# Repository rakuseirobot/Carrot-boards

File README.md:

# Carrot-boards
全自動走行台車の回路図です。
[Carrotの動画はこちら](https://www.youtube.com/watch?v=5gtot_12dCg&ab_channel=DDProjectII)

# Features

* STM32F7 Discovery用のボード
* KeyHolder FT234を使ったUSBシリアル変換器
* UI 操作板の基板データ　F4書き込みや、電源、リセットスイッチなどを載せる
* mainboard main基板　raspberryPiやSTM32F4が載ります

# Requirement

* Autodesk Eagleを用いて作成しました。

F4のプログラムは[こちら](https://github.com/rakuseirobot/Carrot-F4-motor)
RaspberryPiのプログラムは[こちら](https://github.com/rakuseirobot/Carrot-ROS-src)

# Note

mainboardに搭載されているSTM32F446に配線されているイーサネットICはLANコネクタを向きを逆に配置してしまったこととおそらく配線を間違ってしまったこともあり、実装すると3.3Vラインがショートしてしまうため注意してください。

# Author

* Shun Kayaki
* Kyushu institute of Technology
* shun@guetan.dev

# License

Copyright (c) 2019 Shun Kayaki
Released under the MIT license

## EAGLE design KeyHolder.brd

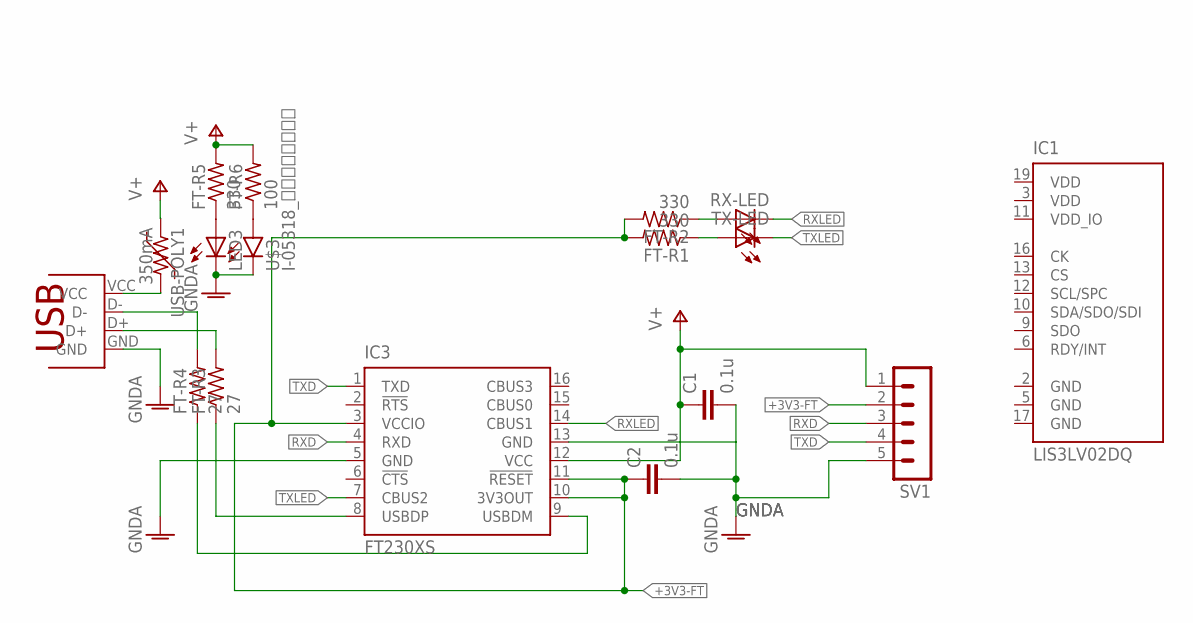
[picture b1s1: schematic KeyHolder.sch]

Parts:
C1, C2: 0.1u; C1608
FT-R1, FT-R2, FT-R5: 330; R0805
FT-R3, FT-R4: 27; R0805
FT-R6: 100; R0805
IC1: LIS3LV02DQ; QFPN-28
IC3: FT230XS; SSOP16
LED3: LEDCHIP-LED0805; CHIP-LED0805
RX-LED: LEDCHIP-LED0805; CHIP-LED0805
SV1: MA05-1
TX-LED: LEDCHIP-LED0805; CHIP-LED0805
U$2: USB-PAD; USB
U$3: I-05318_ＮＳＳＷ１５７Ｔ; NSSW157T
USB-POLY1: 350mA; F0805MP

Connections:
+3V3-FT: C2.1, FT-R1.2, FT-R2.2, IC3.3 (VCCIO), IC3.10 (3V3OUT), IC3.11 (!RESET), SV1.2
GND: IC1.2 (GND), IC1.5 (GND), IC1.17 (GND)
GNDA: C1.2, C2.2, IC3.5 (GND), IC3.13 (GND), LED3.C, SV1.5, U$2.GND, U$3.CATHODE (C)
unnamed: FT-R2.1, RX-LED.A
unnamed: FT-R1.1, TX-LED.A
unnamed: FT-R3.2, U$2.D+
unnamed: FT-R3.1, IC3.8 (USBDP)
unnamed: FT-R4.1, IC3.9 (USBDM)
unnamed: FT-R4.2, U$2.D-
unnamed: U$2.VCC, USB-POLY1.2
unnamed: FT-R5.1, LED3.A
unnamed: FT-R6.1, U$3.ANODE (A)
RXD: IC3.4 (RXD), SV1.3
RXLED: IC3.14 (CBUS1), RX-LED.C
TXD: IC3.1 (TXD), SV1.4
TXLED: IC3.7 (CBUS2), TX-LED.C
V+: C1.1, FT-R5.2, FT-R6.2, IC3.12 (VCC), SV1.1, USB-POLY1.1
VDD: IC1.3 (VDD), IC1.19 (VDD)
VDD_IO: IC1.11 (VDD_IO)

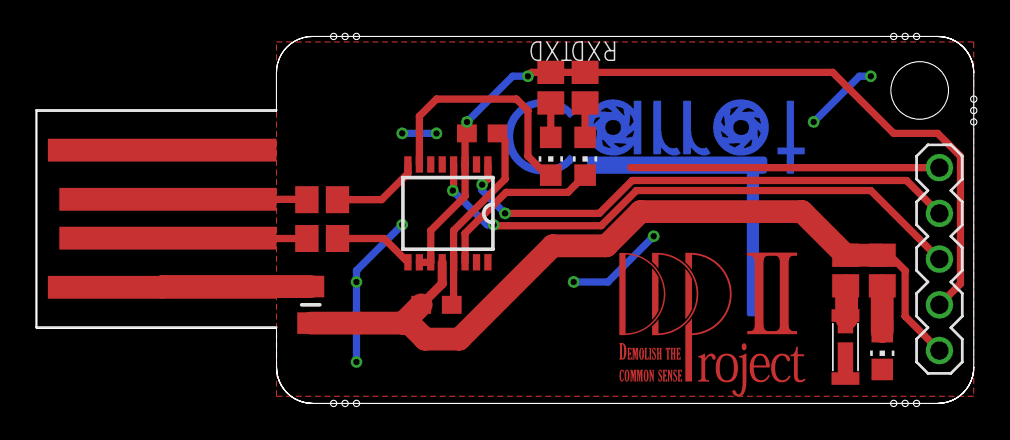
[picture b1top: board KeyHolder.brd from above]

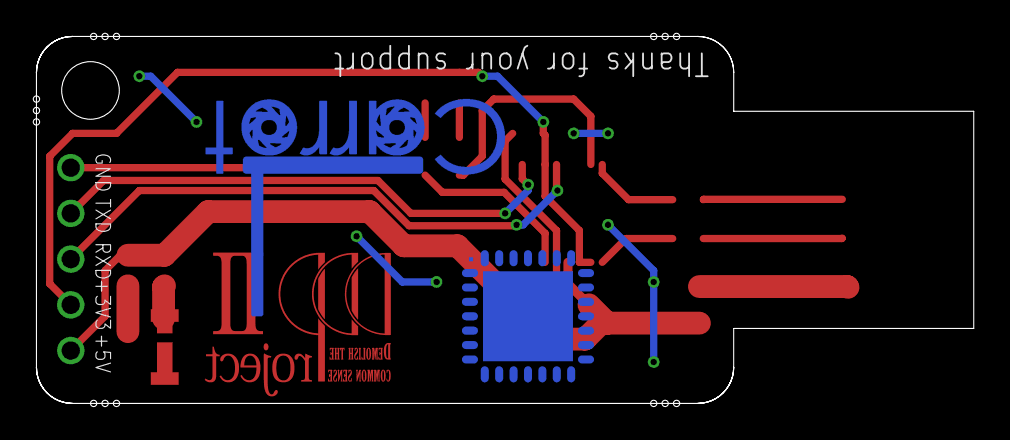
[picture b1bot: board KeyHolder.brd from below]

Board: 2 copper layers, 52.1 x 20.4 mm, 19 parts (2 on the bottom side), 18 nets.

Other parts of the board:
U$5: CARROT
U$6: DDPROJECT2-TOP

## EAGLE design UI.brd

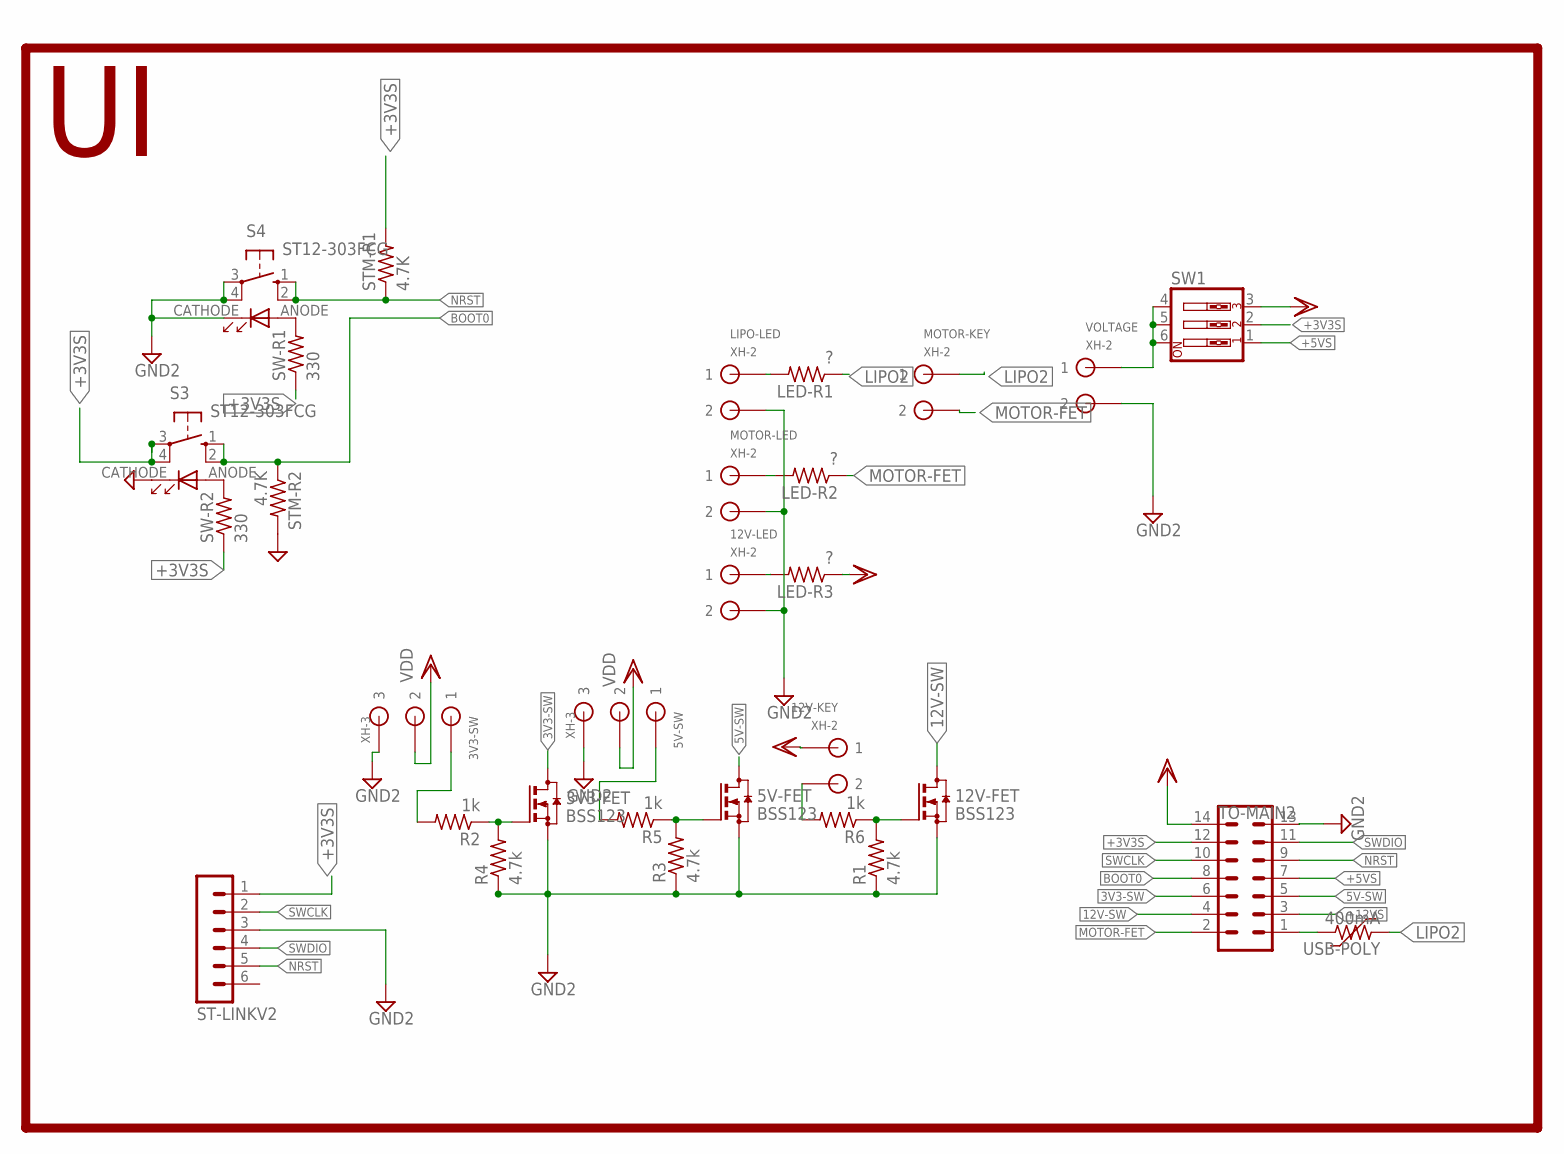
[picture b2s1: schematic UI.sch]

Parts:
3V3-FET, 5V-FET, 12V-FET: BSS123; SOT23
3V3-SW, 5V-SW: XH-3; CON3
12V-KEY, 12V-LED: XH-2; CON2
LED-R1, LED-R2, LED-R3: ?; M0805
LIPO-LED: XH-2; CON2
MOTOR-KEY: XH-2; CON2
MOTOR-LED: XH-2; CON2
R1, R3, R4: 4.7k; M0805
R2, R5, R6: 1k; M0805
S3, S4: ST12-303FCG; ST12303FCG
ST-LINKV2: MA06-1
STM-R1, STM-R2: 4.7K; R0805
SW1: SW_DIP-3; EDG-03
SW-R1, SW-R2: 330; R0805
TO-MAIN2: ML14
USB-POLY: 400mA; MF-5/1
VOLTAGE: XH-2; CON2

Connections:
3V3-SW: 3V3-FET.3 (D), TO-MAIN2.6
5V-SW: 5V-FET.3 (D), TO-MAIN2.5
12V-SW: 12V-FET.3 (D), TO-MAIN2.4
+3V3S: S3.3, S3.4, ST-LINKV2.1, STM-R1.2, SW1.2, SW-R1.1, SW-R2.1, TO-MAIN2.12
+5VS: SW1.1, TO-MAIN2.7
+12VS: TO-MAIN2.3
BOOT0: S3.1, S3.2, STM-R2.1, TO-MAIN2.8
GND2: 3V3-FET.2 (S), 3V3-SW.P$3 (3), 5V-FET.2 (S), 5V-SW.P$3 (3), 12V-FET.2 (S), 12V-LED.P$2 (2), LIPO-LED.P$2 (2), MOTOR-LED.P$2 (2), R1.1, R3.1, R4.1, S3.CATHODE (C), S4.3, S4.4, S4.CATHODE (C), ST-LINKV2.3, STM-R2.2, TO-MAIN2.13, VOLTAGE.P$2 (2)
LIPO2: LED-R1.1, MOTOR-KEY.P$1 (1), USB-POLY.1
MOTOR-FET: LED-R2.1, MOTOR-KEY.P$2 (2), TO-MAIN2.2
unnamed: 3V3-FET.1 (G), R2.1, R4.2
unnamed: 5V-FET.1 (G), R3.2, R5.1
unnamed: SW1.4, SW1.5, SW1.6, VOLTAGE.P$1 (1)
unnamed: 12V-FET.1 (G), R1.2, R6.1
unnamed: 12V-KEY.P$2 (2), R6.2
unnamed: 3V3-SW.P$1 (1), R2.2
unnamed: 5V-SW.P$1 (1), R5.2
unnamed: S4.ANODE (A), SW-R1.2
unnamed: S3.ANODE (A), SW-R2.2
unnamed: TO-MAIN2.1, USB-POLY.2
unnamed: LED-R1.2, LIPO-LED.P$1 (1)
unnamed: LED-R2.2, MOTOR-LED.P$1 (1)
unnamed: 12V-LED.P$1 (1), LED-R3.2
NRST: S4.1, S4.2, ST-LINKV2.5, STM-R1.1, TO-MAIN2.9
SWCLK: ST-LINKV2.2, TO-MAIN2.10
SWDIO: ST-LINKV2.4, TO-MAIN2.11
VDD: 3V3-SW.P$2 (2), 5V-SW.P$2 (2), 12V-KEY.P$1 (1), LED-R3.1, SW1.3, TO-MAIN2.14

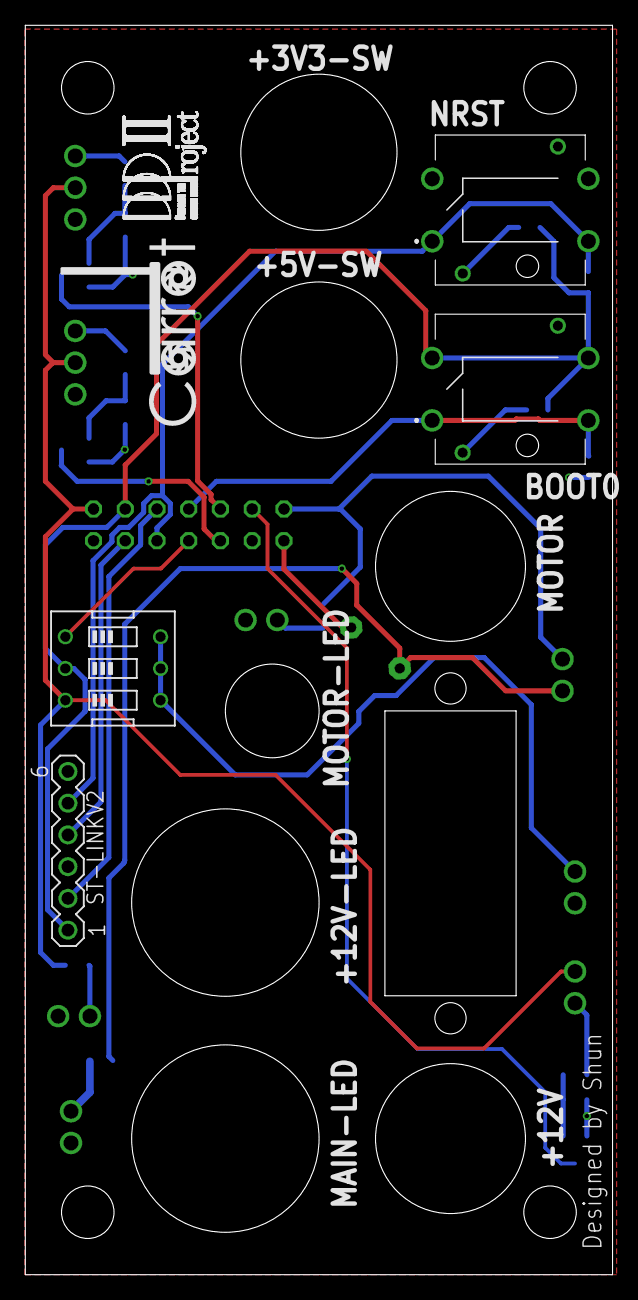
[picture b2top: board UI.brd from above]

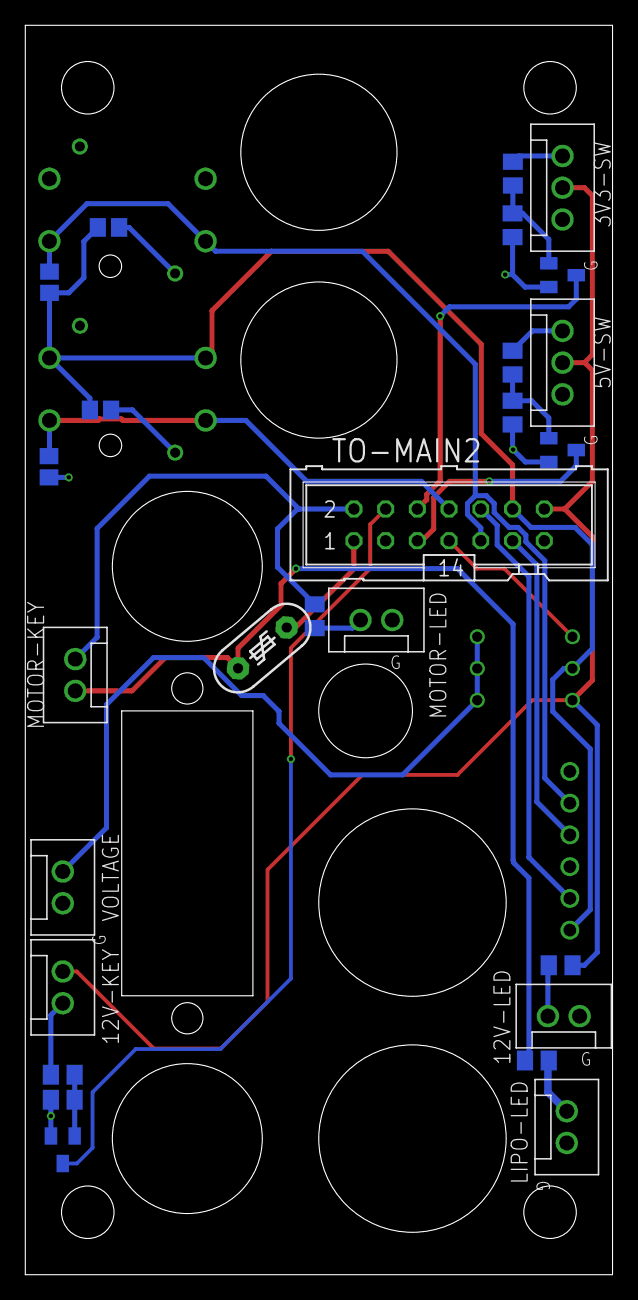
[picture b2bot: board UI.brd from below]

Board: 2 copper layers, 47.0 x 100.0 mm, 32 parts (26 on the bottom side), 26 nets.

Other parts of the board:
U$7: CARROT-SILK
U$8: DDPROJECT2

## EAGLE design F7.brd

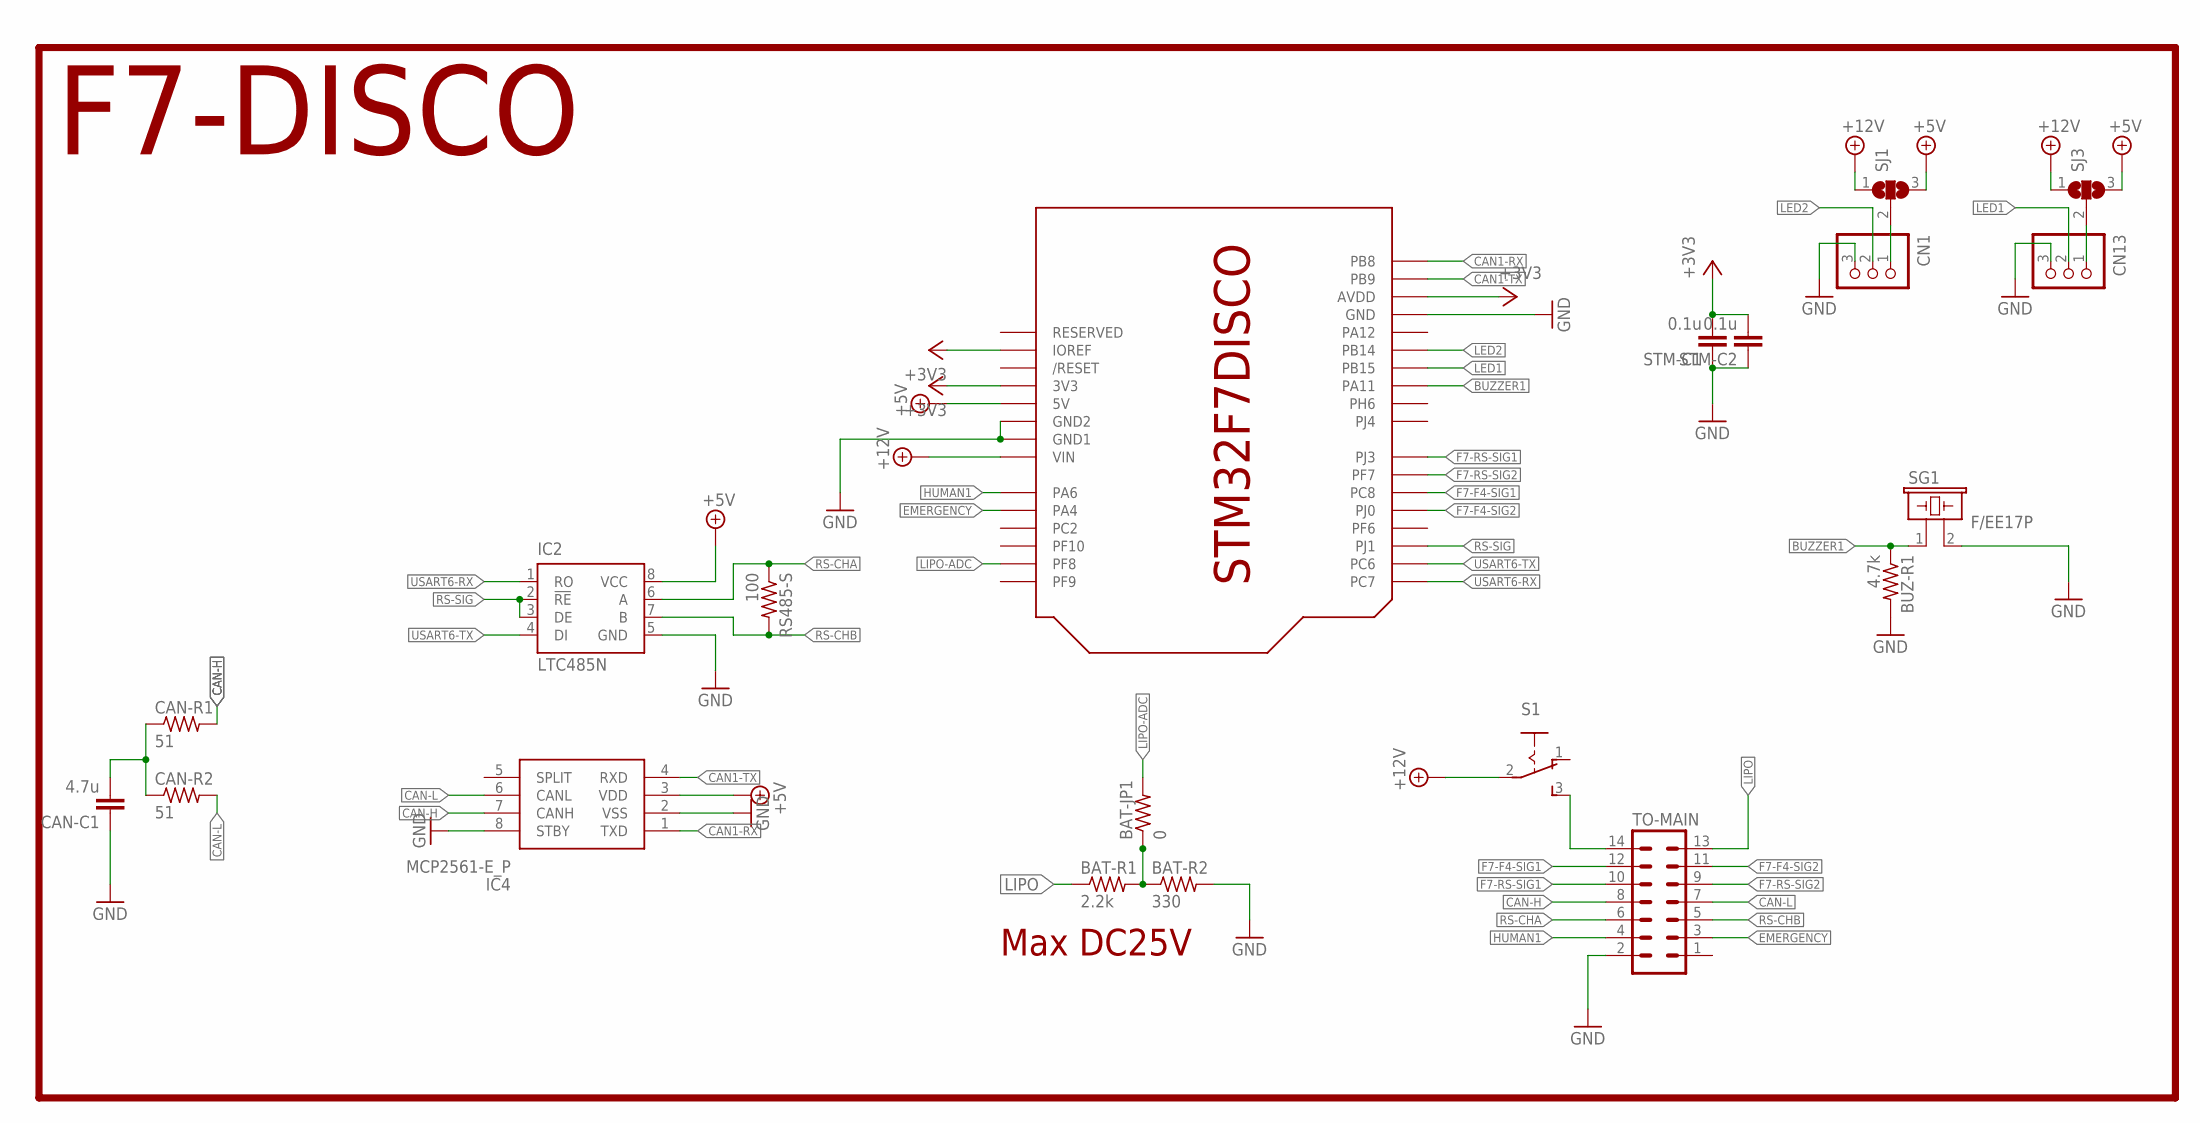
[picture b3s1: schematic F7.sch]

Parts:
BAT-JP1: 0; R0805
BAT-R1: 2.2k; R0805
BAT-R2: 330; R0805
BUZ-R1: 4.7k; R0805
CAN-C1: 4.7u; C0805
CAN-R1, CAN-R2: 51; R0805
CN1, CN13: B3P-VH
IC2: LTC485N; DIL08
IC4: MCP2561-E_P; DIP781W56P254L950H533Q8N
RS485-S: 100; R0805
S1: 255SB
SG1: F/EE17P
SJ1, SJ3: SJ2WW; SJ_2W
STM-C1, STM-C2: 0.1u; C0805
TO-MAIN: ML14
U$1: F7-DISCO-ARDUINO

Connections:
+5V: IC2.8 (VCC), IC4.3 (VDD), SJ1.3, SJ3.3, U$1.5V
+9V: S1.2, SJ1.1, SJ3.1, U$1.VIN
+12V: S1.3 (S), TO-MAIN.14
BUZZER1: BUZ-R1.1, SG1.1, U$1.PA11
CAN1-RX: IC4.1 (TXD), U$1.PB8
CAN1-TX: IC4.4 (RXD), U$1.PB9
CAN-H: CAN-R1.2, IC4.7 (CANH), TO-MAIN.8
CAN-L: CAN-R2.2, IC4.6 (CANL), TO-MAIN.7
EMERGENCY: TO-MAIN.3, U$1.PA4
F7-F4-SIG1: TO-MAIN.12, U$1.PC8
F7-F4-SIG2: TO-MAIN.11, U$1.PJ0
F7-RS-SIG1: TO-MAIN.10, U$1.PJ3
F7-RS-SIG2: TO-MAIN.9, U$1.PF7
GND: BAT-R2.2, BUZ-R1.2, CAN-C1.1, CN1.3, CN13.3, IC2.5 (GND), IC4.2 (VSS), IC4.8 (STBY), SG1.2, STM-C1.1, STM-C2.1, TO-MAIN.2, U$1.GND1 (GND), U$1.GND@1 (GND1), U$1.GND@2 (GND2)
HUMAN1: TO-MAIN.4, U$1.PA6
LED1: CN13.2, U$1.PB15
LED2: CN1.2, U$1.PB14
LIPO: BAT-R1.1, TO-MAIN.13
LIPO-ADC: BAT-JP1.2, U$1.PF8
unnamed: CN1.1, SJ1.2
unnamed: CAN-C1.2, CAN-R1.1, CAN-R2.1
unnamed: BAT-JP1.1, BAT-R1.2, BAT-R2.1
unnamed: CN13.1, SJ3.2
RS-CHA: IC2.6 (A), RS485-S.1, TO-MAIN.6
RS-CHB: IC2.7 (B), RS485-S.2, TO-MAIN.5
RS-SIG: IC2.2 (!RE), IC2.3 (DE), U$1.PJ1
USART6-RX: IC2.1 (RO), U$1.PC7
USART6-TX: IC2.4 (DI), U$1.PC6
VCC: STM-C1.2, STM-C2.2, U$1.3V (3V3), U$1.AVDD, U$1.IOREF

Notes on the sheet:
Max DC25V
F7-DISCO

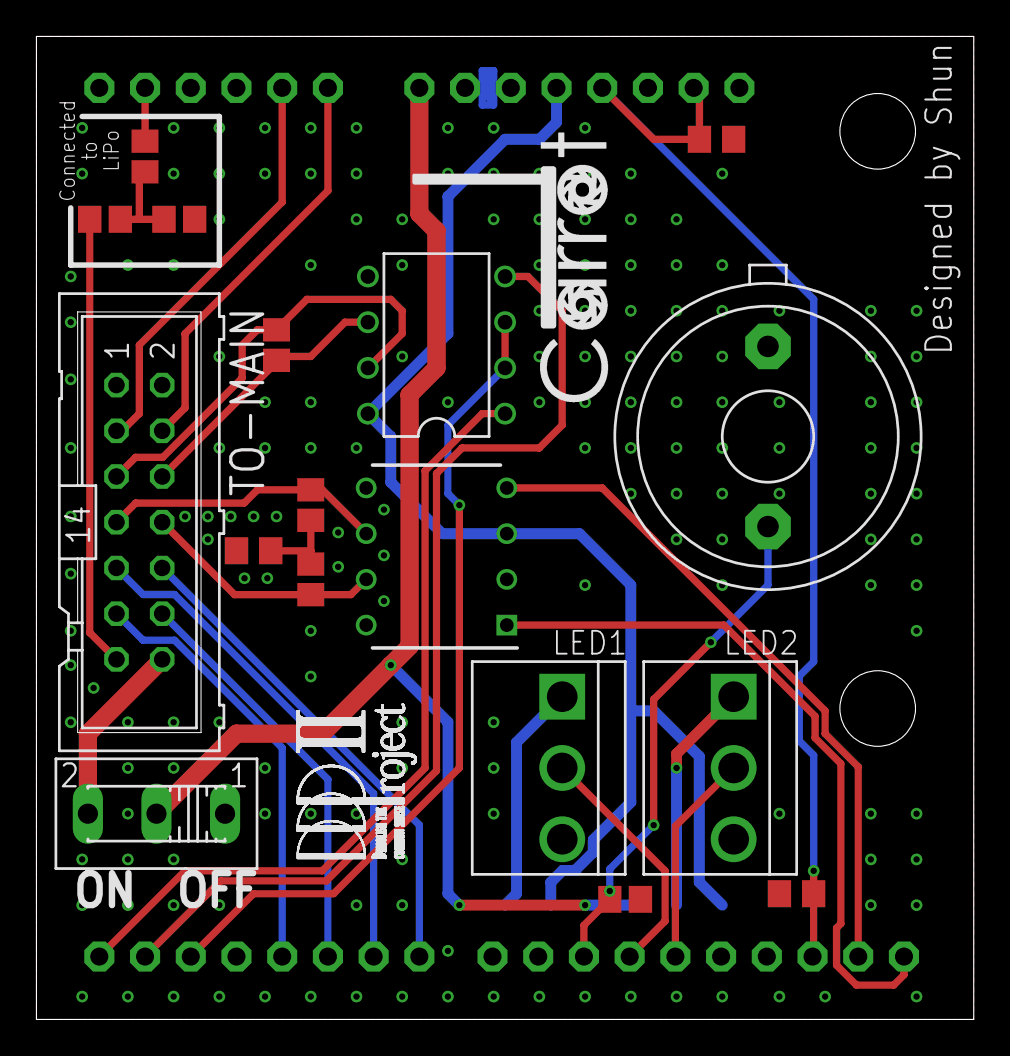
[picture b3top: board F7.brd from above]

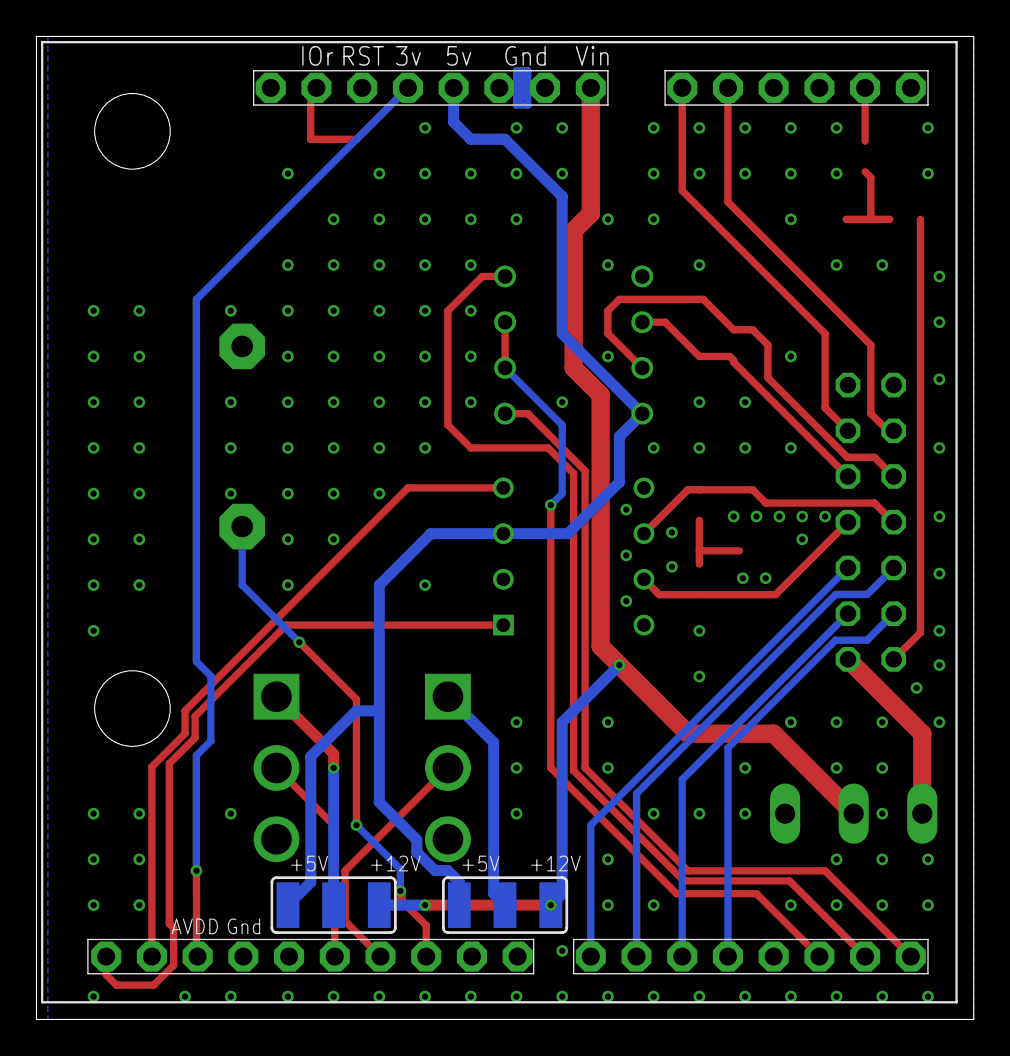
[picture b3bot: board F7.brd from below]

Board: 2 copper layers, 52.1 x 54.6 mm, 22 parts (3 on the bottom side), 29 nets.

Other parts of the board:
U$4: CARROT-SILK
U$9: DDPROJECT2

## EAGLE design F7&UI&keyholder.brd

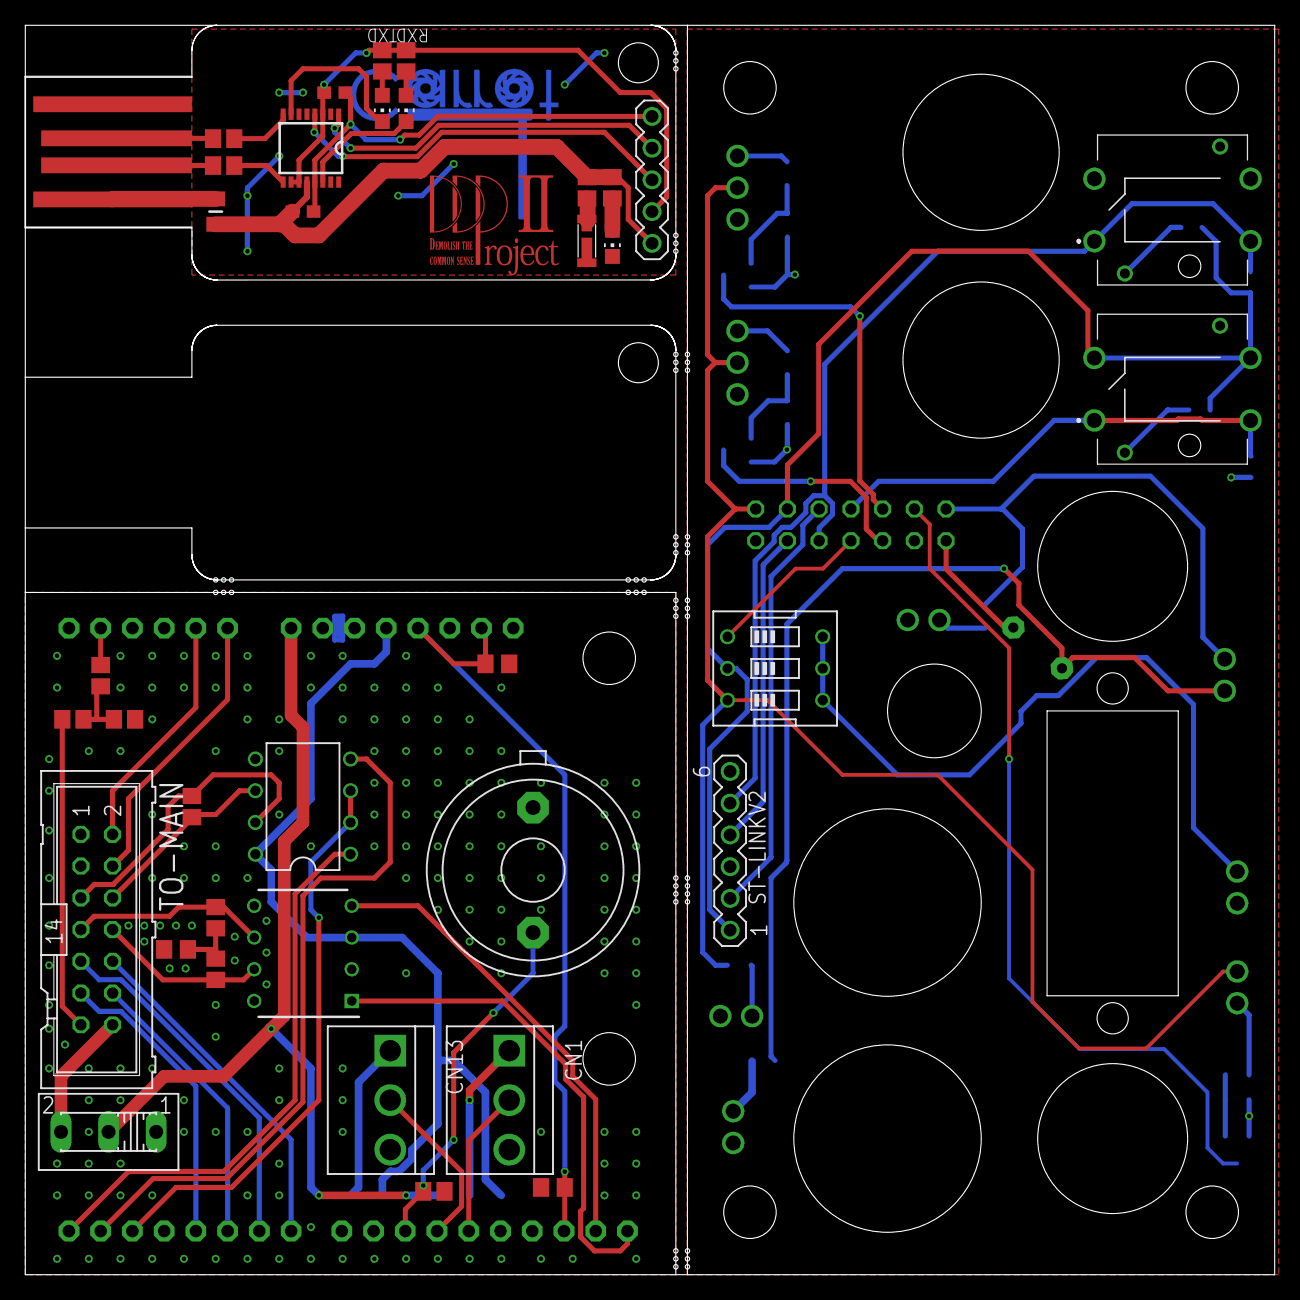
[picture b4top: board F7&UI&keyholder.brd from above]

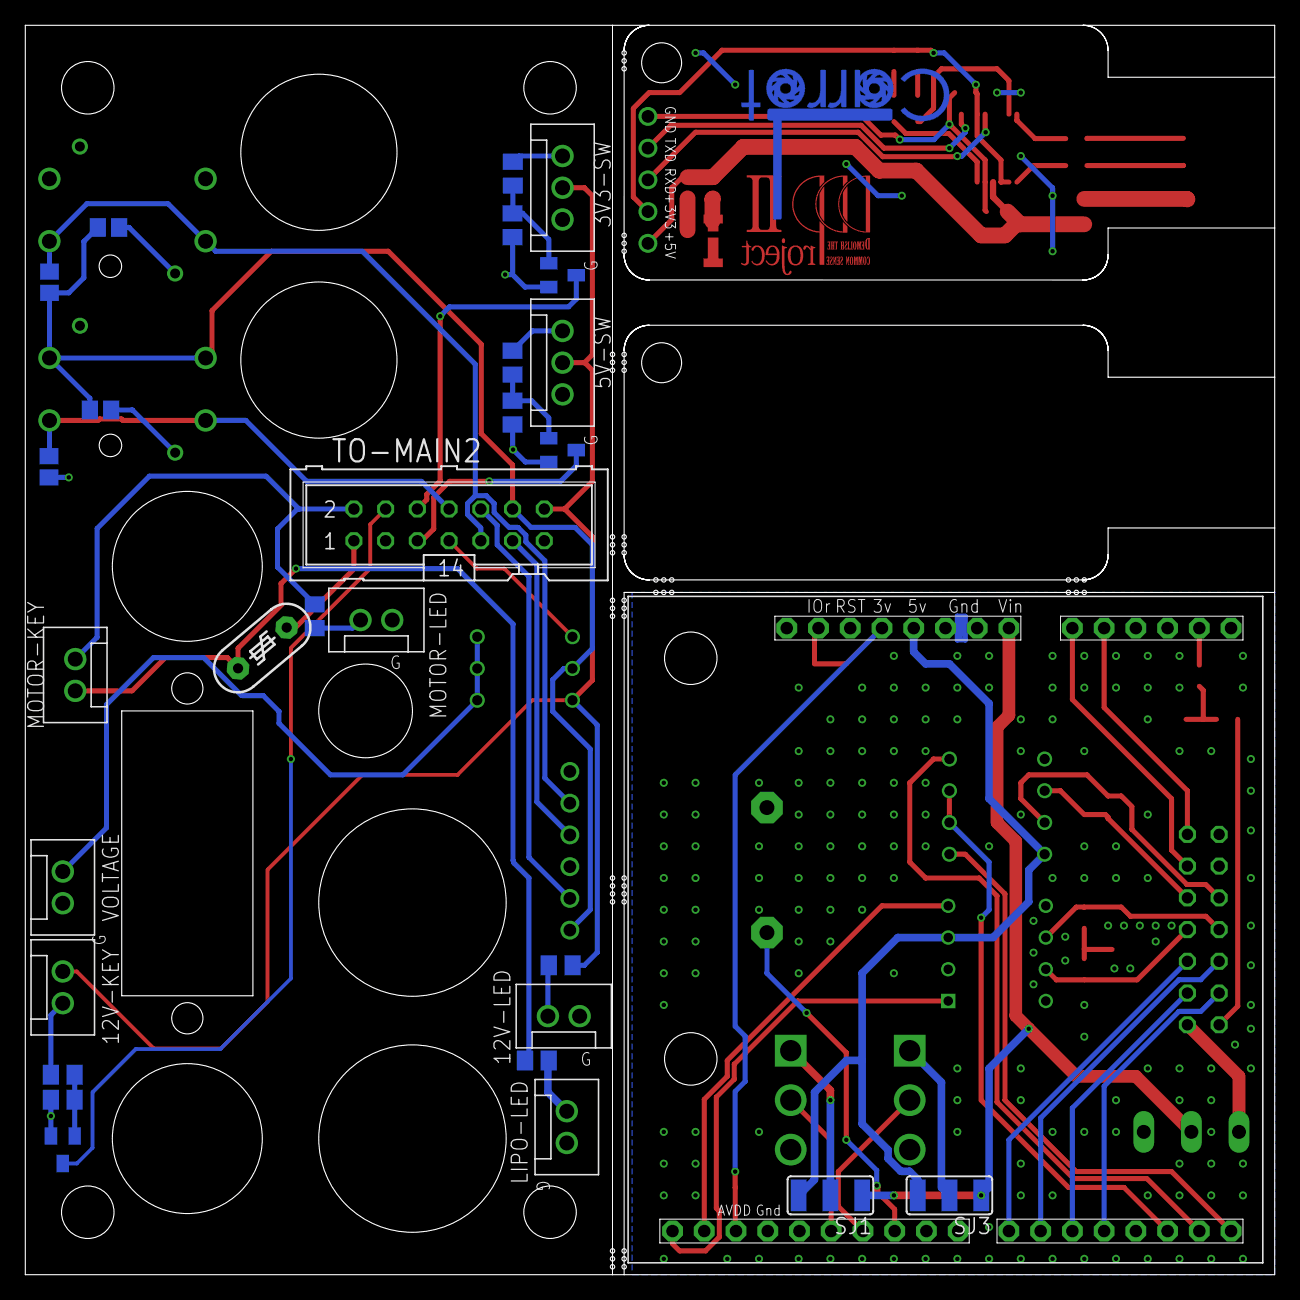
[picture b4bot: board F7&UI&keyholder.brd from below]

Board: 2 copper layers, 100.0 x 100.0 mm, 68 parts (30 on the bottom side), 72 nets.

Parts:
3V3-FET, 5V-FET, 12V-FET: BSS123; SOT23
3V3-SW, 5V-SW: XH-3; CON3
12V-KEY, 12V-LED: XH-2; CON2
BAT-JP1: 0; R0805
BAT-R1: 2.2k; R0805
BAT-R2: 330; R0805
BUZ-R1: 4.7k; R0805
C1, C2: 0.1u; C1608
CAN-C1: 4.7u; C0805
CAN-R1, CAN-R2: 51; R0805
CN1, CN13: B3P-VH
FT-R1, FT-R2, FT-R5: 330; R0805
FT-R3, FT-R4: 27; R0805
FT-R6: 100; R0805
IC2: LTC485N; DIL08
IC3: FT230XS; SSOP16
IC4: MCP2561-E_P; DIP781W56P254L950H533Q8N
LED3: CHIP-LED0805
LED-R1, LED-R2, LED-R3: ?; M0805
LIPO-LED: XH-2; CON2
MOTOR-KEY: XH-2; CON2
MOTOR-LED: XH-2; CON2
R1, R3, R4: 4.7k; M0805
R2, R5, R6: 1k; M0805
RS485-S: 100; R0805
RX-LED: CHIP-LED0805
S1: 255SB
S3, S4: ST12-303FCG; ST12303FCG
SG1: F/EE17P
SJ1, SJ3: SJ_2W
ST-LINKV2: MA06-1
STM-C1, STM-C2: 0.1u; C0805
STM-R1, STM-R2: 4.7K; R0805
SV1: MA05-1
SW1: EDG-03
SW-R1, SW-R2: 330; R0805
TO-MAIN, TO-MAIN2: ML14
TX-LED: CHIP-LED0805
U$1: F7-DISCO-ARDUINO
U$2: USB-PAD; USB
U$3: I-05318_ＮＳＳＷ１５７Ｔ; NSSW157T
U$5: CARROT
U$6: DDPROJECT2-TOP
USB-POLY: 400mA; MF-5/1
USB-POLY1: 350mA; F0805MP
VOLTAGE: XH-2; CON2

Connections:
3V3-SW: 3V3-FET.3, TO-MAIN2.6
5V-SW: 5V-FET.3, TO-MAIN2.5
12V-SW: 12V-FET.3, TO-MAIN2.4
+3V3-FT: C2.1, FT-R1.2, FT-R2.2, IC3.3, IC3.10, IC3.11, SV1.2
+3V3S: S3.3, S3.4, ST-LINKV2.1, STM-R1.2, SW1.2, SW-R1.1, SW-R2.1, TO-MAIN2.12
+5V: IC2.8, IC4.3, SJ1.3, SJ3.3, U$1.5V
+5VS: SW1.1, TO-MAIN2.7
+9V: S1.2, SJ1.1, SJ3.1, U$1.VIN
+12V: S1.3, TO-MAIN.14
BOOT0: S3.1, S3.2, STM-R2.1, TO-MAIN2.8
BUZZER1: BUZ-R1.1, SG1.1, U$1.PA11
CAN1-RX: IC4.1, U$1.PB8
CAN1-TX: IC4.4, U$1.PB9
CAN-H: CAN-R1.2, IC4.7, TO-MAIN.8
CAN-L: CAN-R2.2, IC4.6, TO-MAIN.7
EMERGENCY: TO-MAIN.2, U$1.PA4
F7-F4-SIG1: TO-MAIN.12, U$1.PC8
F7-F4-SIG2: TO-MAIN.11, U$1.PJ0
F7-RS-SIG1: TO-MAIN.10, U$1.PJ3
F7-RS-SIG2: TO-MAIN.9, U$1.PF7
GND: BAT-R2.2, BUZ-R1.2, CAN-C1.1, CN1.3, CN13.3, IC2.5, IC4.2, IC4.8, SG1.2, STM-C1.1, STM-C2.1, TO-MAIN.1, U$1.GND1, U$1.GND@1, U$1.GND@2
GND2: 3V3-FET.2, 3V3-SW.P$3, 5V-FET.2, 5V-SW.P$3, 12V-FET.2, 12V-LED.P$2, LIPO-LED.P$2, MOTOR-LED.P$2, R1.1, R3.1, R4.1, S3.CATHODE, S4.3, S4.4, S4.CATHODE, ST-LINKV2.3, STM-R2.2, TO-MAIN2.13, VOLTAGE.P$2
GNDA: IC3.5, LED3.C, U$2.GND, U$3.CATHODE
HUMAN1: TO-MAIN.4, U$1.PA6
LED1: CN13.2, U$1.PB15
LED2: CN1.2, U$1.PB14
LIPO: BAT-R1.1, TO-MAIN.13
LIPO2: LED-R1.1, MOTOR-KEY.P$1, USB-POLY.1
LIPO-ADC: BAT-JP1.2, U$1.PF8
MOTOR-FET: LED-R2.1, MOTOR-KEY.P$2, TO-MAIN2.2
unnamed: CN1.1, SJ1.2
unnamed: 3V3-FET.1, R2.1, R4.2
unnamed: 5V-FET.1, R3.2, R5.1
unnamed: CAN-C1.2, CAN-R1.1, CAN-R2.1
unnamed: SW1.4, SW1.5, SW1.6, VOLTAGE.P$1
unnamed: 12V-FET.1, R1.2, R6.1
unnamed: 12V-KEY.P$2, R6.2
unnamed: 3V3-SW.P$1, R2.2
unnamed: 5V-SW.P$1, R5.2
unnamed: S4.ANODE, SW-R1.2
unnamed: S3.ANODE, SW-R2.2
unnamed: TO-MAIN2.1, USB-POLY.2
unnamed: LED-R1.2, LIPO-LED.P$1
unnamed: LED-R2.2, MOTOR-LED.P$1
unnamed: 12V-LED.P$1, LED-R3.2
unnamed: FT-R2.1, RX-LED.A
unnamed: FT-R1.1, TX-LED.A
unnamed: FT-R3.2, U$2.D+
unnamed: FT-R3.1, IC3.8
unnamed: FT-R4.1, IC3.9
unnamed: FT-R4.2, U$2.D-
unnamed: C1.2, C2.2, IC3.13, SV1.5
unnamed: U$2.VCC, USB-POLY1.2
unnamed: FT-R5.1, LED3.A
unnamed: FT-R6.1, U$3.ANODE
unnamed: BAT-JP1.1, BAT-R1.2, BAT-R2.1
unnamed: CN13.1, SJ3.2
NRST: S4.1, S4.2, ST-LINKV2.5, STM-R1.1, TO-MAIN2.9
RS-CHA: IC2.6, RS485-S.1, TO-MAIN.6
RS-CHB: IC2.7, RS485-S.2, TO-MAIN.5
RS-SIG: IC2.2, IC2.3, U$1.PJ1
RXD: IC3.4, SV1.3
RXLED: IC3.14, RX-LED.C
SWCLK: ST-LINKV2.2, TO-MAIN2.10
SWDIO: ST-LINKV2.4, TO-MAIN2.11
TXD: IC3.1, SV1.4
TXLED: IC3.7, TX-LED.C
USART6-RX: IC2.1, U$1.PC7
USART6-TX: IC2.4, U$1.PC6
V+: C1.1, FT-R5.2, FT-R6.2, IC3.12, SV1.1, USB-POLY1.1
VCC: STM-C1.2, STM-C2.2, U$1.3V, U$1.AVDD, U$1.IOREF
VDD: 3V3-SW.P$2, 5V-SW.P$2, 12V-KEY.P$1, LED-R3.1, SW1.3, TO-MAIN2.14

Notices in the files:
parts and their libraries:
polyswitch: Copyright (C) 2008, Bob Starr
